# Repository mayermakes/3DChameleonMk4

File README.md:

Welcome to the 3DChameleon 4 Color Changer Source Respository

Please use this as a basis for your own multi color solution, whether that be commerical or private.  The whole idea of the 3DChameleon is to bring color printing to everyone.  Use this, learn from it, improve it, share it... make 3D printing beautiful!

This project is 100% open source using the MIT Open Source license.  The original Tinkercad files are here: https://www.tinkercad.com/things/4nptaDc06M6-3dchameleon-40-current-version

Copyright 2024 William J. Steele

Permission is hereby granted, free of charge, to any person obtaining a copy of this software and associated documentation files (the “Software”), to deal in the Software without restriction, including without limitation the rights to use, copy, modify, merge, publish, distribute, sublicense, and/or sell copies of the Software, and to permit persons to whom the Software is furnished to do so, subject to the following conditions:

The above copyright notice and this permission notice shall be included in all copies or substantial portions of the Software.

THE SOFTWARE IS PROVIDED “AS IS”, WITHOUT WARRANTY OF ANY KIND, EXPRESS OR IMPLIED, INCLUDING BUT NOT LIMITED TO THE WARRANTIES OF MERCHANTABILITY, FITNESS FOR A PARTICULAR PURPOSE AND NONINFRINGEMENT. IN NO EVENT SHALL THE AUTHORS OR COPYRIGHT HOLDERS BE LIABLE FOR ANY CLAIM, DAMAGES OR OTHER LIABILITY, WHETHER IN AN ACTION OF CONTRACT, TORT OR OTHERWISE, ARISING FROM, OUT OF OR IN CONNECTION WITH THE SOFTWARE OR THE USE OR OTHER DEALINGS IN THE SOFTWARE.

3D Brookesia:
This is a derivative variant of the 3D Chameleon Mk4 electronics, made for hand assembly (some smd soldering required).
changes:
MCU changed from ATmega328 to ATtiny3226
4 Leds added to show selected tool.
pluggable Screw terminal connectors
fits Hammond 1455 Series Case
TMC2209 Stepper drivers
Diode based bootup protection for Stepper drivers
Thermistor controlled Fan to keep electronics cool when used in 3D printer enclosure.
Reverse Voltage Protection on Inputs

The mechanical parts are unchanged.

3D Brookesia Variant by Clem "mayermakes" Mayer published under the same License as the original.
The name refers to a number of tiny chameleon species (Brookesia sp.) because it runs on ATtiny 
Link to video regarding this variant: publishing Date TBD
Link to additional ressources: TBD

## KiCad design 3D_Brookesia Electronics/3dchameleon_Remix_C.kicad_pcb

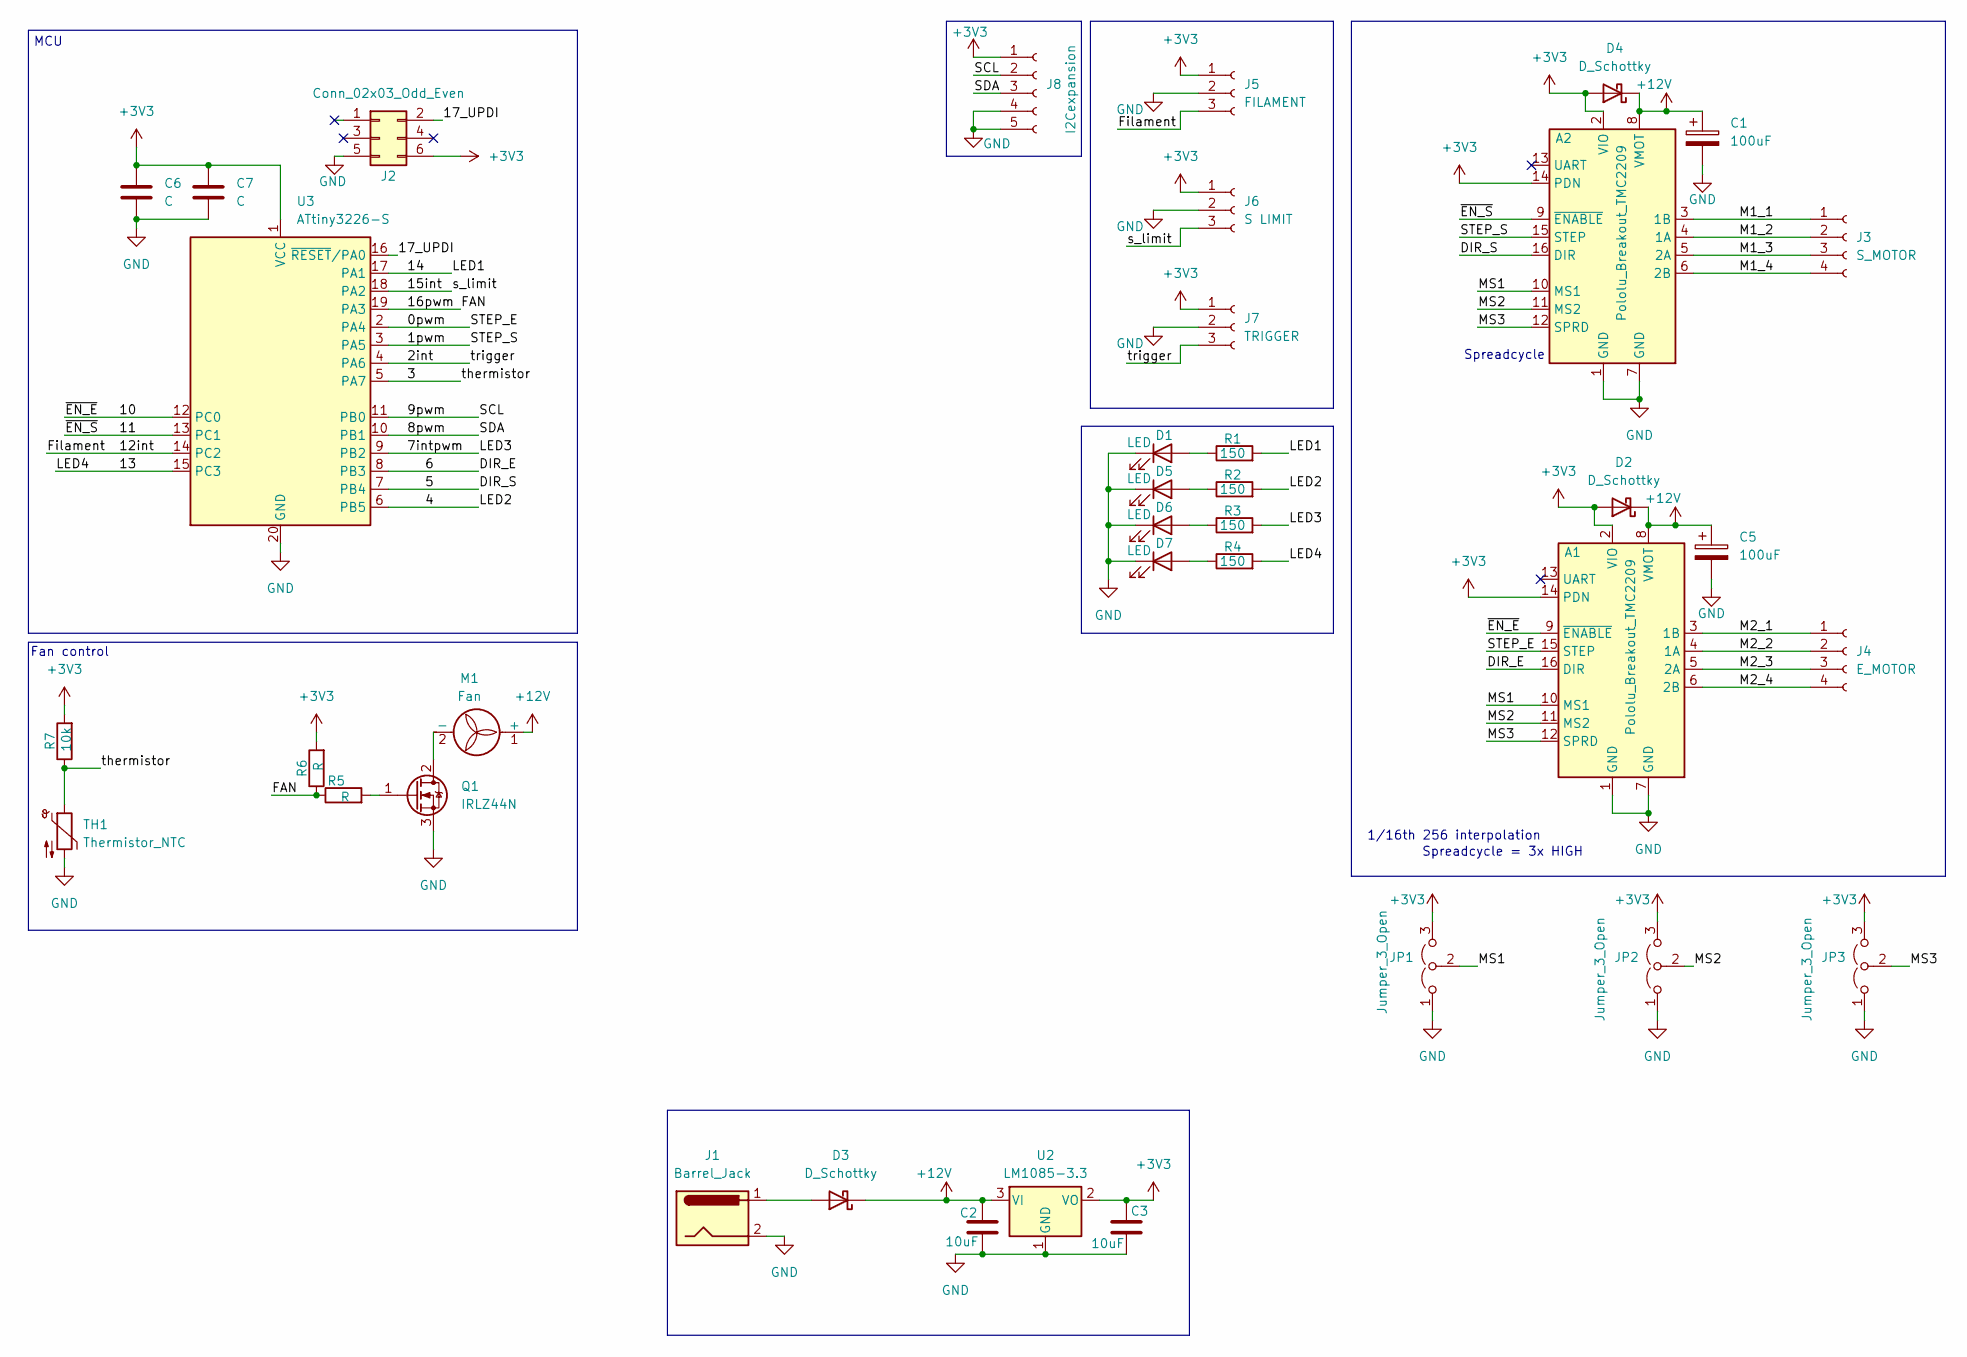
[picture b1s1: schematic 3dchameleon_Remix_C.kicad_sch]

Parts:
A1, A2: Pololu_Breakout_TMC2209; Pololu_Breakout-16_15.2x20.3mm
C1, C5: 100uF; CP_Radial_D10.0mm_P5.00mm
C2, C3: 10uF; C_0603_1608Metric
C6, C7: C; C_0603_1608Metric
D1, D5, D6, D7: LED; LED_D5.0mm
D2, D3, D4: D_Schottky; D_0603_1608Metric
J1: Barrel_Jack; BarrelJack_Horizontal
J2: Conn_02x03_Odd_Even; PinHeader_2x03_P2.54mm_Vertical
J3: S_MOTOR; TerminalBlock_bornier-4_P5.08mm
J4: E_MOTOR; TerminalBlock_bornier-4_P5.08mm
J5: FILAMENT; TerminalBlock_bornier-3_P5.08mm
J6: S LIMIT; TerminalBlock_bornier-3_P5.08mm
J7: TRIGGER; TerminalBlock_bornier-3_P5.08mm
J8: I2Cexpansion; PinHeader_1x05_P2.54mm_Vertical
JP1, JP2, JP3: Jumper_3_Open; SolderJumper-3_P1.3mm_Open_RoundedPad1.0x1.5mm
M1: Fan; PinHeader_1x02_P2.54mm_Vertical
Q1: IRLZ44N; TO-220-3_Horizontal_TabUp
R1, R2, R3, R4: 150; R_0603_1608Metric
R5, R6: R; R_0603_1608Metric
R7: 10k; R_0603_1608Metric
TH1: Thermistor_NTC; R_Axial_DIN0614_L14.3mm_D5.7mm_P5.08mm_Vertical
U2: LM1085-3.3; TO-263-3_TabPin2
U3: ATtiny3226-S; SOIC-20W_7.5x12.8mm_P1.27mm

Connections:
+3V3: A1.2 (VIO), A1.14 (PDN), A2.2 (VIO), A2.14 (PDN), C3.1, C6.1, C7.1, D2.2 (A), D4.2 (A), J2.6, J5.1, J6.1, J7.1, J8.1, JP1.3 (B), JP2.3 (B), JP3.3 (B), R6.2, R7.2, U2.2 (VO), U3.1 (VCC)
+12V: A1.8 (VMOT), A2.8 (VMOT), C1.1, C2.1, C5.1, D2.1 (K), D3.1 (K), D4.1 (K), M1.1 (+), U2.3 (VI)
/0pwm: A1.15 (STEP), U3.2 (PA4)
/1pwm: A2.15 (STEP), U3.3 (PA5)
/2int: J7.3, U3.4 (PA6)
/3: R7.1, TH1.1, U3.5 (PA7)
/4: R2.2, U3.6 (PB5)
/5: A2.16 (DIR), U3.7 (PB4)
/6: A1.16 (DIR), U3.8 (PB3)
/7intpwm: R3.2, U3.9 (PB2)
/8pwm: J8.3, U3.10 (PB1)
/9pwm: J8.2, U3.11 (PB0)
/10: A1.9 (~ENABLE), U3.12 (PC0)
/11: A2.9 (~ENABLE), U3.13 (PC1)
/12int: J5.3, U3.14 (PC2)
/13: R4.2, U3.15 (PC3)
/14: R1.2, U3.17 (PA1)
/15int: J6.3, U3.18 (PA2)
/16pwm: R5.1, R6.1, U3.19 (PA3)
/17_UPDI: J2.2, U3.16 (~RESET/PA0)
/M1_1: A2.3 (1B), J3.1
/M1_2: A2.4 (1A), J3.2
/M1_3: A2.5 (2A), J3.3
/M1_4: A2.6 (2B), J3.4
/M2_1: A1.3 (1B), J4.1
/M2_2: A1.4 (1A), J4.2
/M2_3: A1.5 (2A), J4.3
/M2_4: A1.6 (2B), J4.4
/MS1: A1.10 (MS1), A2.10 (MS1), JP1.2 (C)
/MS2: A1.11 (MS2), A2.11 (MS2), JP2.2 (C)
/MS3: A1.12 (SPRD), A2.12 (SPRD), JP3.2 (C)
GND: A1.1 (GND), A1.7 (GND), A2.1 (GND), A2.7 (GND), C1.2, C2.2, C3.2, C5.2, C6.2, C7.2, D1.1 (K), D5.1 (K), D6.1 (K), D7.1 (K), J1.2, J2.5, J5.2, J6.2, J7.2, J8.4, J8.5, JP1.1 (A), JP2.1 (A), JP3.1 (A), Q1.3 (S), TH1.2, U2.1 (GND), U3.20 (GND)
unnamed: D1.2 (A), R1.1
unnamed: D3.2 (A), J1.1
unnamed: D5.2 (A), R2.1
unnamed: D6.2 (A), R3.1
unnamed: D7.2 (A), R4.1
unnamed: M1.2 (-), Q1.2 (D)
unnamed: Q1.1 (G), R5.2

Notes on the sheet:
Fan control
Spreadcycle = 3x HIGH
MCU
Spreadcycle
1/16th 256 interpolation

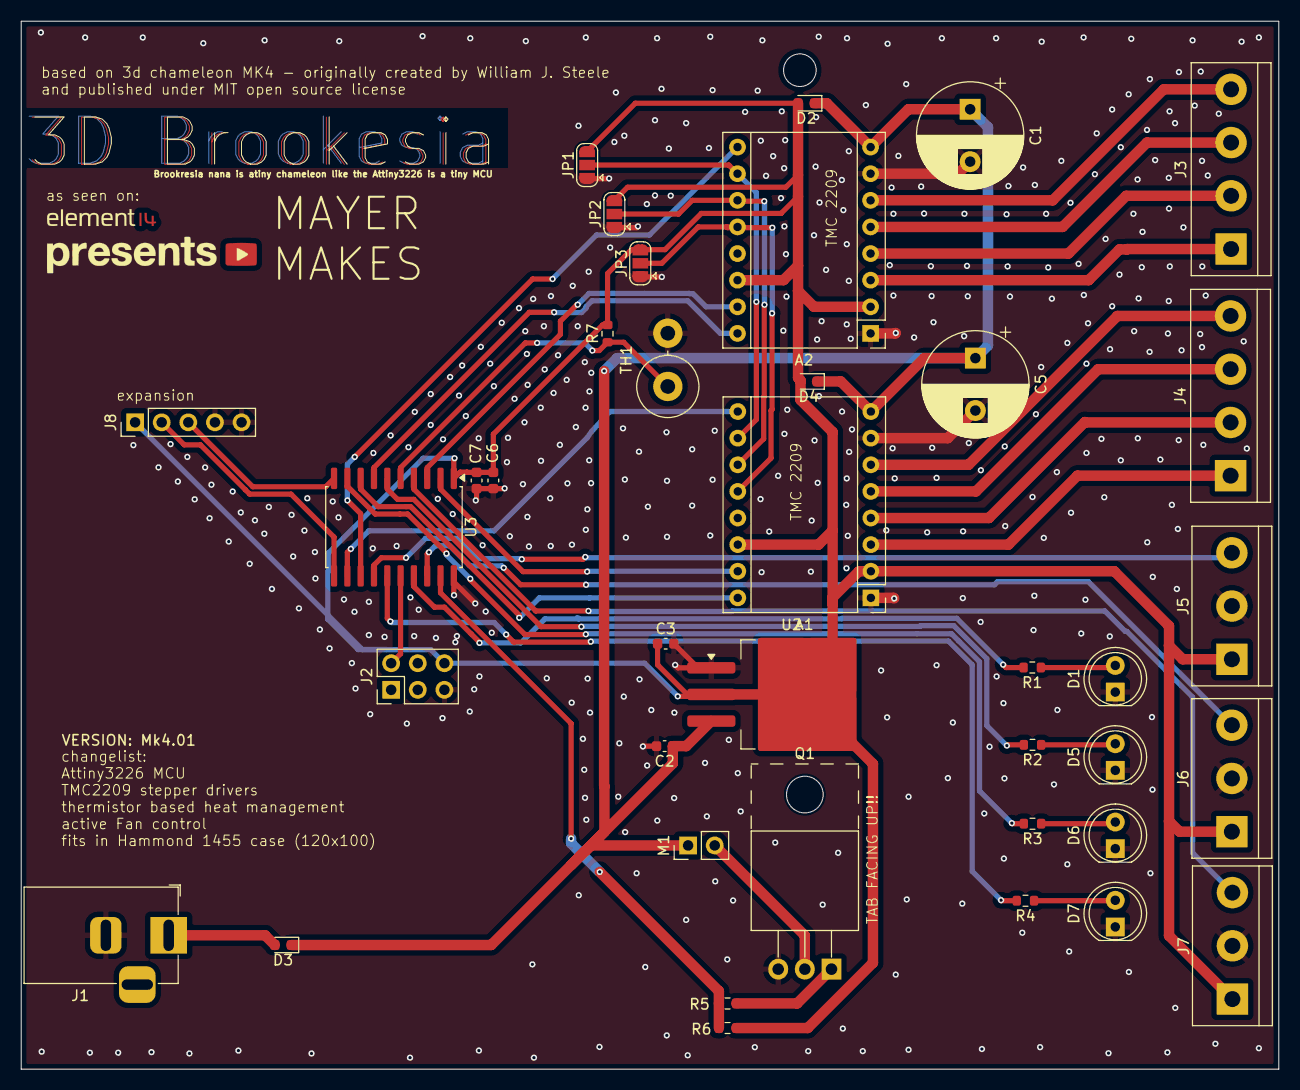
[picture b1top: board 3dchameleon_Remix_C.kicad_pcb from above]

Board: 2 copper layers, 120.0 x 100.0 mm, 39 parts (0 on the bottom side), 39 nets.

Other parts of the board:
Ref**: Val**; e14presents logo 20mm silk and copper v2

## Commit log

2024-11-28 Mk4 Initial Commit
2024-11-28 Initial Mk4 Commit
2024-11-28 Mk4 Electronics, Profiles Commit
2024-11-29 Update SelectorFirmwareMk4.ino
    Updated Revision Date
2025-06-17 Remix of the Electronics with modern parts.
    Code not ported yet.
2025-06-19 Firmware for 3D Brookesia variant
    Changes:
    ported to Attiny3226
    Adds 4 LEDS to show which tool is active
    Adds pwm fan control based on temperature within housing.
2025-06-19 Update README.md
    Added 3d Brookesia Info
2025-06-28 Delete SelectorFirmware_3DBrookesia directory
    replaced with new directory
2025-06-28 Delete Firmware_3DBrookesia directory
    wrong upload
2025-06-28 3D brookesia Firmware

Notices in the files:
3D_Brookesia Electronics/3dchameleon_Remix_C.kicad_pcb:
and published under MIT open source license
